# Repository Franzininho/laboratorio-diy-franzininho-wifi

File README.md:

## Laboratório DIY - Franzininho Wifi

## O que é este projeto?

O projeto **Laboratório DIY - Franzininho Wifi** é um projeto de placa de circuito impresso para facilitar o uso de componentes eletrônicos em oficinas de programação. Este projeto possui um socket para conexão da placa [Franzininho Wifi](https://github.com/Franzininho/Franzininho-WiFi) e diversos periféricos conectados à pinos pré-determinados do socket que podem ser ativados utilizando um conector jumper ou mais.

Esse projeto tem o intuito de auxiliar no ensino de programação utilizando a placa Franzininho Wifi já que muitas vezes nas oficinas de programação com placas microcontroladas é despendido muito tempo para lidar com problemas que vem da manipulação do hardware como utilização da protoabord e realização de conexões. Este tempo muitas vezes acaba prejudicando a atividade já que o tempo onde se foca em fazer as conexões eletrônicas poderia ser melhor aproveitado focando na programação realmente.

Sendo assim, utilizando a facilidade de conexão de periféridos da placa é possível reduzir drásticamente o tempo despendido para conexões eletrônicas, focando no objetivo da oficina, que é a programação.

Esse projeto está sob a licença [CERN-OHL-S v2](https://ohwr.org/cern_ohl_s_v2.txt)

## Como ativar os periféricos?

Os periféricos utilizados na placa são ativados através de pinos de ativação. Esses pinos são compostos por dois pinos macho que devem ser conectados. Um desses pinos macho está conectado ao socket da placa e o outro a um pino do componente eletrônico. Dessa forma, o jumper fecha a conexão entre o componente e a placa microcontrolada.

Como "ativador" para os pinos, recomendo o uso do conector da imagem abaixo. Você pode encontrar esse conector como "jumper com aba", "mini jumper com aba", "jumper cap", entre outros.

Além dos pinos de ativação de sinal que conectam o componente ao socket da placa, existem também os pinos de ativação de energia que são responsáveis por energizar o componente.

## Codificação dos pinos de ativação

Devido à quantidade de pinos de ativação usada na placa, foi preciso desenvolver um sistema de codificação para esses pinos. Esse sistema foi idealizado com cada pino sendo representado por dois algorismos. O primeiro indicando a funcionalidade do pino e o segundo indicando uma numeração do pino. Esse sistema foi utilizado para todos os pinos com exceção dos pinos SDA e SCK. As funções dos primeiros algorismos podem ser vistas abaixo:

| Letra |    Significado    |
| :---: | :---------------: |
|   L   |        LED        |
|   P   |   Piezo Buzzer    |
|   B   |      Botões       |
|   M   |    Servo Motor    |
|   S   |     Sensores      |
|  SDA  |        SDA        |
|  SCK  |        SCK        |
|   E   | Conexões externas |
|   3   |     VCC 3.3V      |
|   5   |      VCC 5V       |

O código correspondente a cada pino de ativação foi impresso ao lado desse pino e o mapeamento dos pinos de ativação para os pinos da placa Franzininho Wifi está impresso na placa e também pode ser acessado [clicando aqui](./mapeamento.md). Além disso, também foi desenvolvida uma biblioteca para uso em conjunto com a placa que permite o uso dos códigos dos pinos de ativação dentro da programação. [Clique aqui para acessar a **biblioteca laboratorioFW-DIY**](https://github.com/Franzininho/biblioteca-laboratorioFW-DIY)

## Como o projeto foi desenvolvido?

O projeto foi desenvolvido com o software [KiCad 7](https://www.kicad.org/). Esse software é aberto e está disponível para Linux, MacOS e Windows.

#### Feito por [LelePG](https://github.com/LelePG)

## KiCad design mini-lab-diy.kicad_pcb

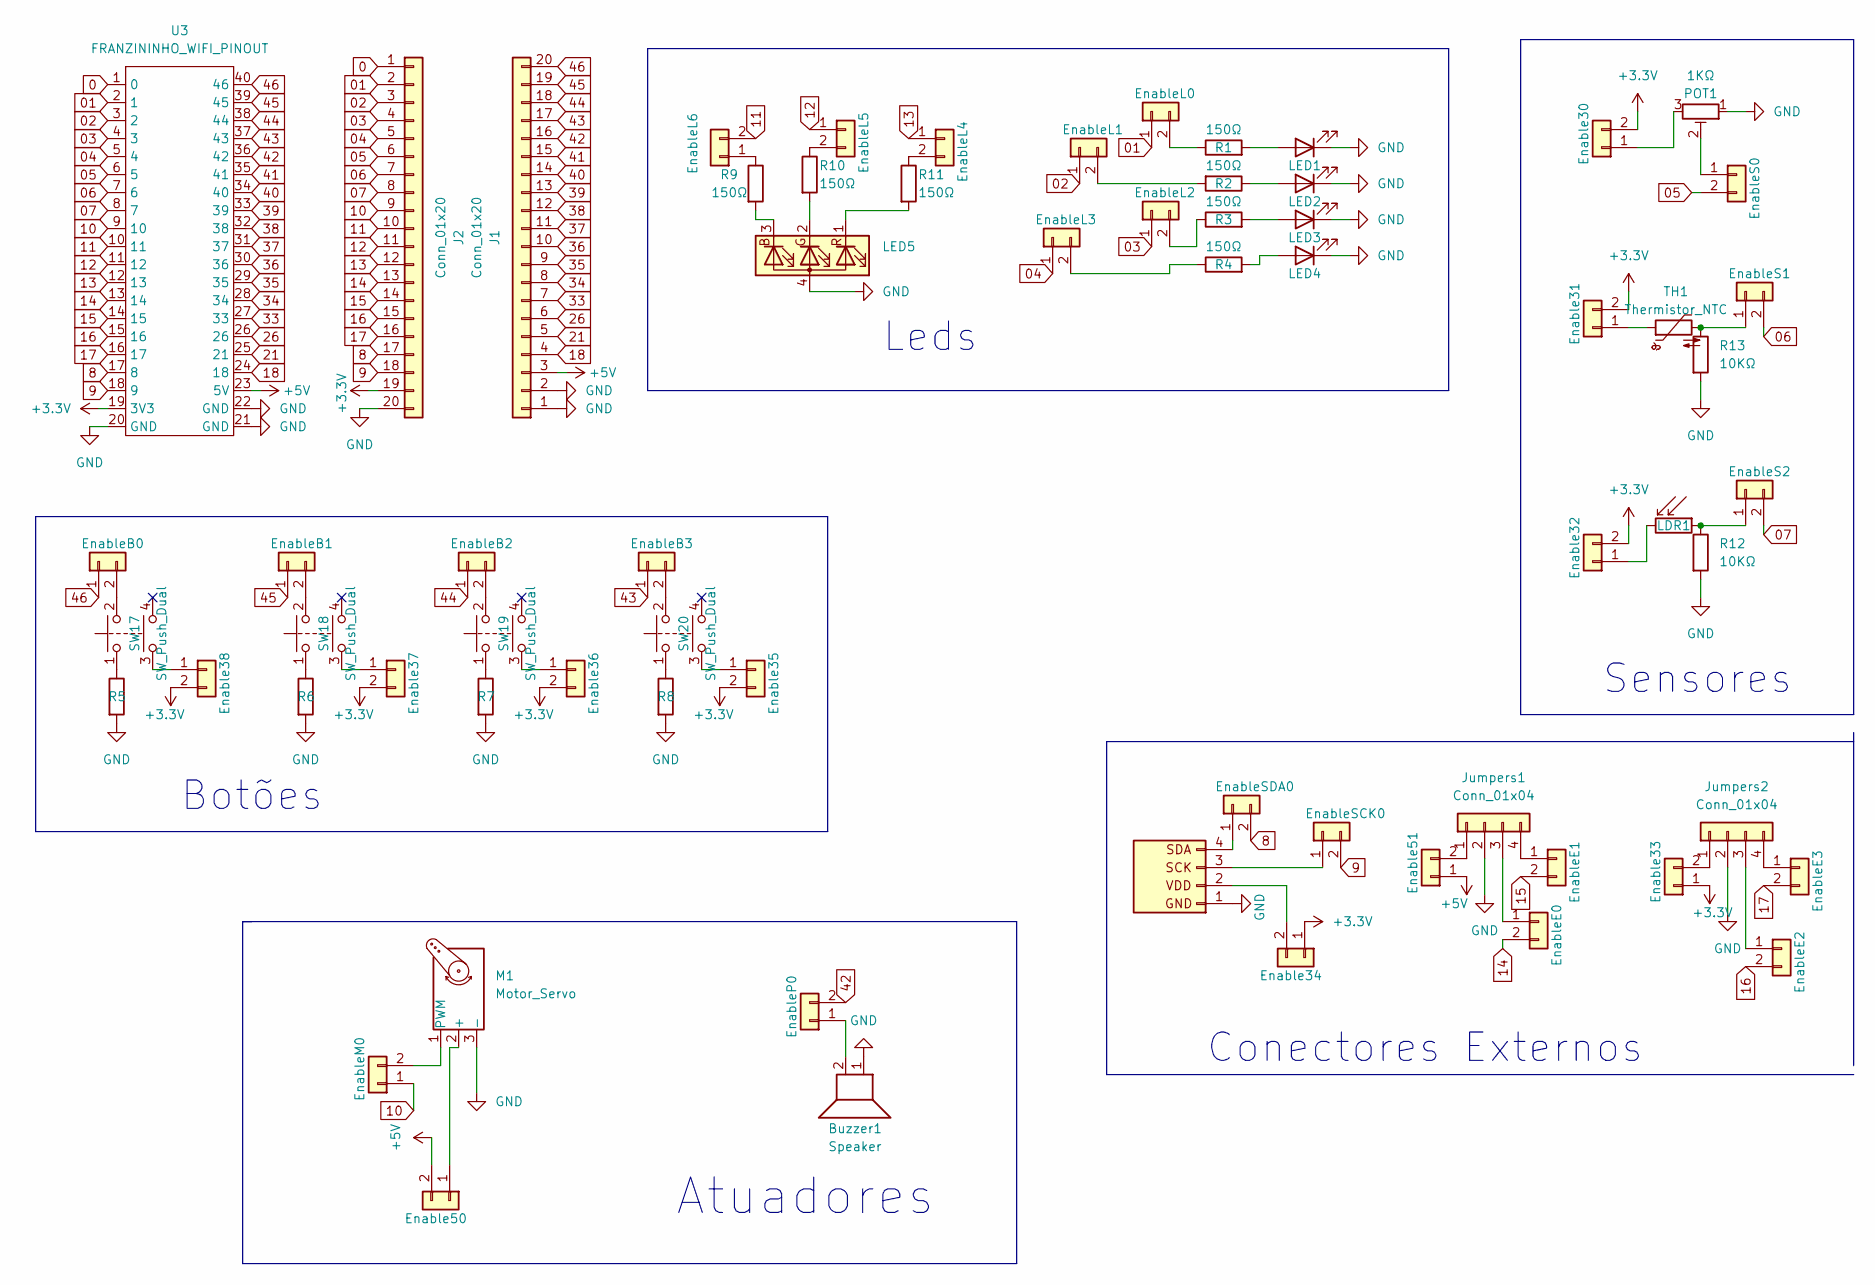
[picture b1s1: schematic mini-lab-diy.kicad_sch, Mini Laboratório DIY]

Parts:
Buzzer1: Speaker; Buzzer_12x9.5RM7.6
D1: LED1; LED_D5.0mm
D2: LED2; LED_D5.0mm
D3: LED3; LED_D5.0mm
D4: LED4; LED_D5.0mm
Enable30, Enable31, Enable32, Enable33, Enable34, Enable35, Enable36, Enable37, Enable38, Enable50, Enable51: Conn_01x02; PinHeader_1x02_P2.54mm_Vertical
EnableB0, EnableB1, EnableB2, EnableB3: Conn_01x02; PinHeader_1x02_P2.54mm_Vertical
EnableE0, EnableE1, EnableE2, EnableE3: Conn_01x02; PinHeader_1x02_P2.54mm_Vertical
EnableL0, EnableL1, EnableL2, EnableL3, EnableL4, EnableL5, EnableL6: Conn_01x02; PinHeader_1x02_P2.54mm_Vertical
EnableM0: Conn_01x02; PinHeader_1x02_P2.54mm_Vertical
EnableP0: Conn_01x02; PinHeader_1x02_P2.54mm_Vertical
EnableS0, EnableS1, EnableS2: Conn_01x02; PinHeader_1x02_P2.54mm_Vertical
EnableSCK0: Conn_01x02; PinHeader_1x02_P2.54mm_Vertical
EnableSDA0: Conn_01x02; PinHeader_1x02_P2.54mm_Vertical
J1, J2: Conn_01x20; PinHeader_1x20_P2.54mm_Vertical
Jumpers1, Jumpers2: Conn_01x04; PinHeader_1x04_P2.54mm_Vertical
LDR1: LDR07; R_LDR_5.1x4.3mm_P3.4mm_Vertical
LED5: LED_RGBA; LED_D5.0mm-4_RGB
M1: Motor_Servo; PinHeader_1x03_P2.54mm_Vertical
POT1: 1KΩ; Potentiometer_Bourns_PTV09A-1_Single_Vertical
R1, R2, R3, R4, R5, R6, R7, R8, R9, R10, R11: 150Ω; R_Axial_DIN0204_L3.6mm_D1.6mm_P7.62mm_Horizontal
R12, R13: 10KΩ; R_Axial_DIN0204_L3.6mm_D1.6mm_P7.62mm_Horizontal
SW17, SW18, SW19, SW20: SW_Push_Dual; Switch
TH1: Thermistor_NTC; PinHeader_2x01_P2.54mm_Vertical
Tela1: Conn_01x04; PinHeader_1x04_P2.54mm_Vertical
U3: FRANZININHO_WIFI_PINOUT

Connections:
0: J2.1, U3.1 (0)
01: EnableL0.1, J2.2, U3.2 (1)
02: EnableL1.1, J2.3, U3.3 (2)
03: EnableL2.1, J2.4, U3.4 (3)
04: EnableL3.1, J2.5, U3.5 (4)
05: EnableS0.2, J2.6, U3.6 (5)
06: EnableS1.2, J2.7, U3.7 (6)
07: EnableS2.2, J2.8, U3.8 (7)
8: EnableSDA0.2, J2.17, U3.17 (8)
9: EnableSCK0.2, J2.18, U3.18 (9)
10: EnableM0.1, J2.9, U3.9 (10)
11: EnableL6.2, J2.10, U3.10 (11)
12: EnableL5.1, J2.11, U3.11 (12)
13: EnableL4.1, J2.12, U3.12 (13)
14: EnableE0.2, J2.13, U3.13 (14)
15: EnableE1.2, J2.14, U3.14 (15)
16: EnableE2.2, J2.15, U3.15 (16)
17: EnableE3.2, J2.16, U3.16 (17)
18: J1.4, U3.24 (18)
21: J1.5, U3.25 (21)
26: J1.6, U3.26
33: J1.7, U3.27 (33)
34: J1.8, U3.28 (34)
35: J1.9, U3.29 (35)
36: J1.10, U3.30 (36)
37: J1.11, U3.31 (37)
38: J1.12, U3.32 (38)
39: J1.13, U3.33 (39)
40: J1.14, U3.34 (40)
41: J1.15, U3.35 (41)
42: EnableP0.2, J1.16, U3.36 (42)
43: EnableB3.1, J1.17, U3.37 (43)
44: EnableB2.1, J1.18, U3.38 (44)
45: EnableB1.1, J1.19, U3.39 (45)
46: EnableB0.1, J1.20, U3.40 (46)
+3.3V: Enable30.2, Enable31.2, Enable32.2, Enable33.1, Enable34.1, Enable35.2, Enable36.2, Enable37.2, Enable38.2, J2.19, U3.19 (3V3)
+5V: Enable50.2, Enable51.1, J1.3, U3.23 (5V)
GND: Buzzer1.1, D1.1 (K), D2.1 (K), D3.1 (K), D4.1 (K), J1.1, J1.2, J2.20, Jumpers1.2, Jumpers2.2, LED5.4 (A), M1.3 (-), POT1.1, R5.2, R6.2, R7.2, R8.2, R12.2, R13.2, Tela1.1, U3.20 (GND), U3.21 (GND), U3.22 (GND)
unnamed: D1.2 (A), R1.2
unnamed: D2.2 (A), R2.1
unnamed: D3.2 (A), R3.2
unnamed: D4.2 (A), R4.2
unnamed: Enable30.1, POT1.3
unnamed: Enable31.1, TH1.1
unnamed: Enable32.1, LDR1.2
unnamed: Enable33.2, Jumpers2.1
unnamed: Enable34.2, Tela1.2
unnamed: Enable35.1, SW20.3
unnamed: Enable36.1, SW19.3
unnamed: Enable37.1, SW18.3
unnamed: Enable38.1, SW17.3
unnamed: Enable50.1, M1.2 (+)
unnamed: Enable51.2, Jumpers1.1
unnamed: EnableB0.2, SW17.2
unnamed: EnableB1.2, SW18.2
unnamed: EnableB2.2, SW19.2
unnamed: EnableB3.2, SW20.2
unnamed: EnableE0.1, Jumpers1.3
unnamed: EnableE1.1, Jumpers1.4
unnamed: EnableE2.1, Jumpers2.3
unnamed: EnableE3.1, Jumpers2.4
unnamed: EnableL0.2, R1.1
unnamed: EnableL1.2, R2.2
unnamed: EnableL2.2, R3.1
unnamed: EnableL3.2, R4.1
unnamed: EnableL4.2, R11.1
unnamed: EnableL5.2, R10.1
unnamed: EnableL6.1, R9.1
unnamed: EnableM0.2, M1.1 (PWM)
unnamed: Buzzer1.2, EnableP0.1
unnamed: EnableS0.1, POT1.2
unnamed: EnableS1.1, R13.1, TH1.2
unnamed: EnableS2.1, LDR1.1, R12.1
unnamed: EnableSCK0.1, Tela1.3
unnamed: EnableSDA0.1, Tela1.4
unnamed: LED5.3 (BK), R9.2
unnamed: LED5.2 (GK), R10.2
unnamed: LED5.1 (RK), R11.2
unnamed: R5.1, SW17.1
unnamed: R6.1, SW18.1
unnamed: R7.1, SW19.1
unnamed: R8.1, SW20.1

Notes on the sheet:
Leds
Conectores Externos
Botões
Atuadores
Sensores

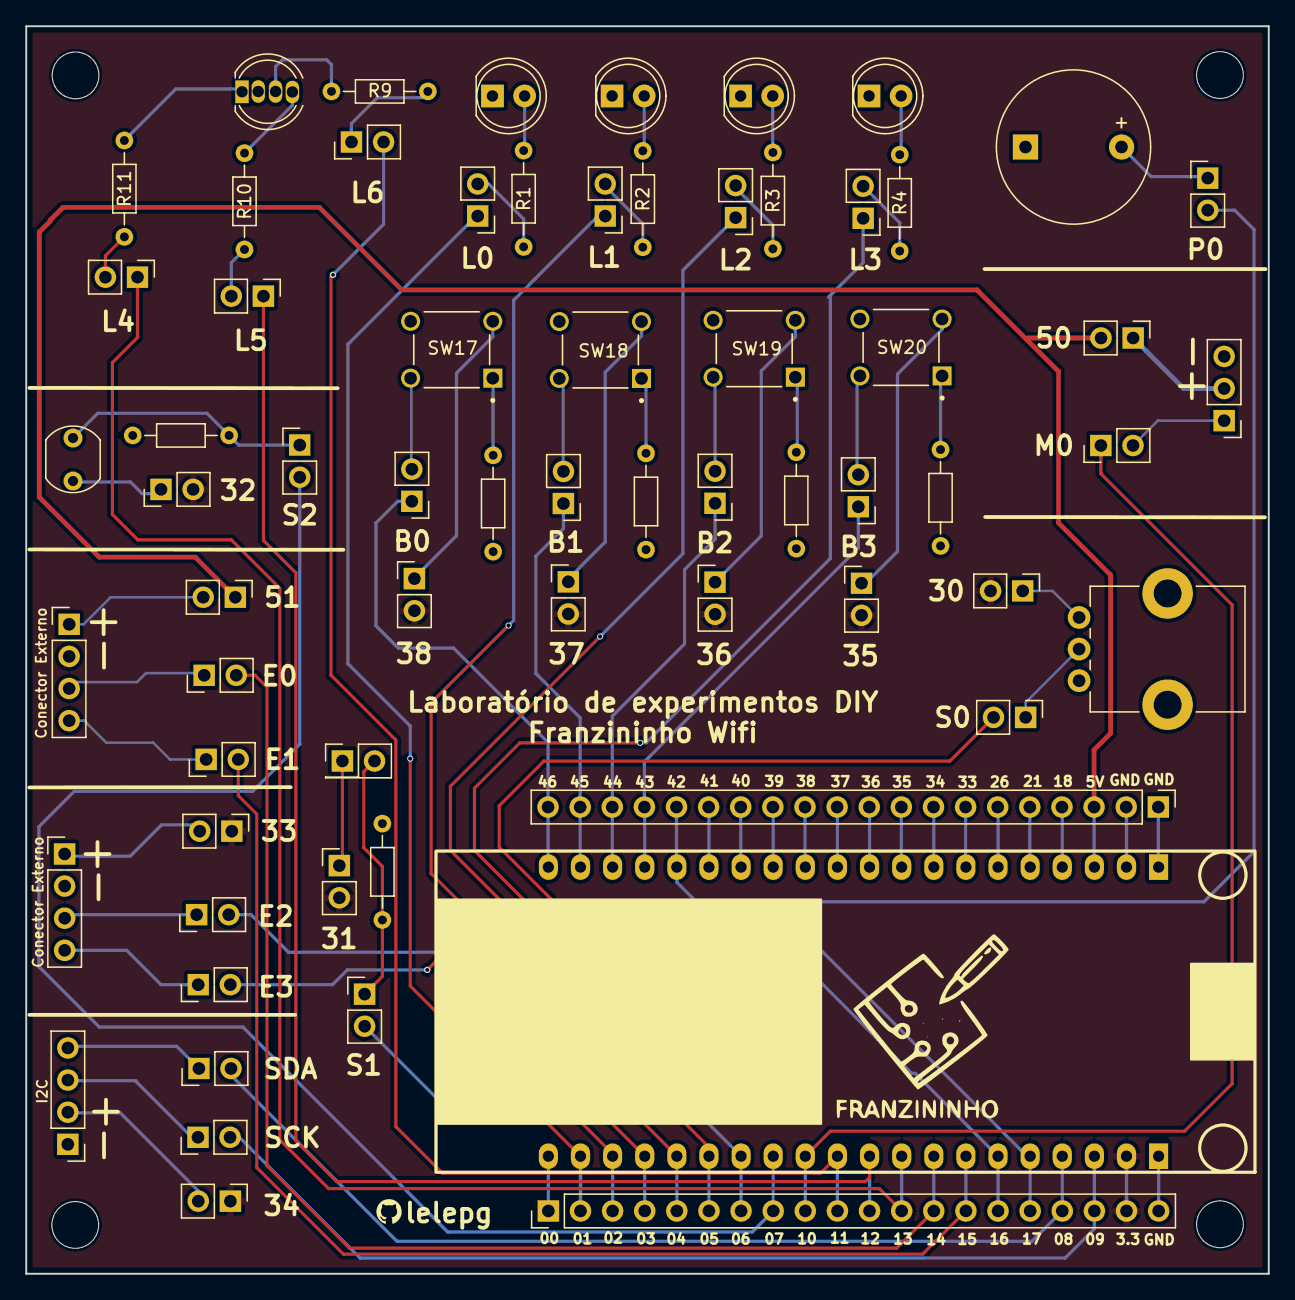
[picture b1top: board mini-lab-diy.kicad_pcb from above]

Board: 2 copper layers, 98.3 x 98.7 mm, 66 parts (0 on the bottom side), 82 nets.

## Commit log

2023-08-06 commit inicial
2024-01-08 modificação de orientação de alguns pads
2024-05-27 retirada dos gnd do led rgb e do motor, e aumento no espaçamento dos dados da silk
